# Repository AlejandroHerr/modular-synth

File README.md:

# Modular Synth

KiCad designs for DIY Eurorack modular synthesizer modules.

## Acknowledgements

This project is based on the work of [Erica Synths](https://www.ericasynths.lv/) and [Moritz Klein](https://www.youtube.com/@MoritzKlein0), in particular their collaboration on the **mki x es.EDU** DIY series: nine educational kits (sequencer, VCO, wavefolder, noise/S&H, mixer, VCF, envelope generator, dual VCA, and output stereo mixer with headphone amp) that walk through the design of analog synth circuits step by step. The VCO was the first kit released.

Moritz Klein's YouTube series explaining the circuit design is the main reference. All credit for the original circuit designs goes to them.

## Contents

- `vco/`: KiCad project for a sawtooth-core analog VCO (schematic and PCB), with a separate power block schematic.
- `vcf/`: KiCad project for a VCF (schematic and PCB).
- `envelope-generator/`: KiCad project for an envelope generator (schematic only for now, the PCB is not laid out yet).

## References

- [Erica Synths and Moritz Klein set to release DIY synthesiser kits (Mixdown)](https://mixdownmag.com.au/news/erica-synths-and-moritz-klein-set-to-release-diy-synthesiser-kits/)
- [Erica Synths mki x es.EDU VCO (Synth Anatomy)](https://www.synthanatomy.com/2021/12/mki-x-es-edu-vco-first-education-diy-module-from-erica-synths-and-moritz-klein.html)
- [DIY Eurorack series kicks off with Erica Synths and Moritz Klein (CDM)](https://cdm.link/2022/01/diy-eurorack-series-kicks-off-with-erica-synths-and-moritz-klein-mki-x-es-edu/)

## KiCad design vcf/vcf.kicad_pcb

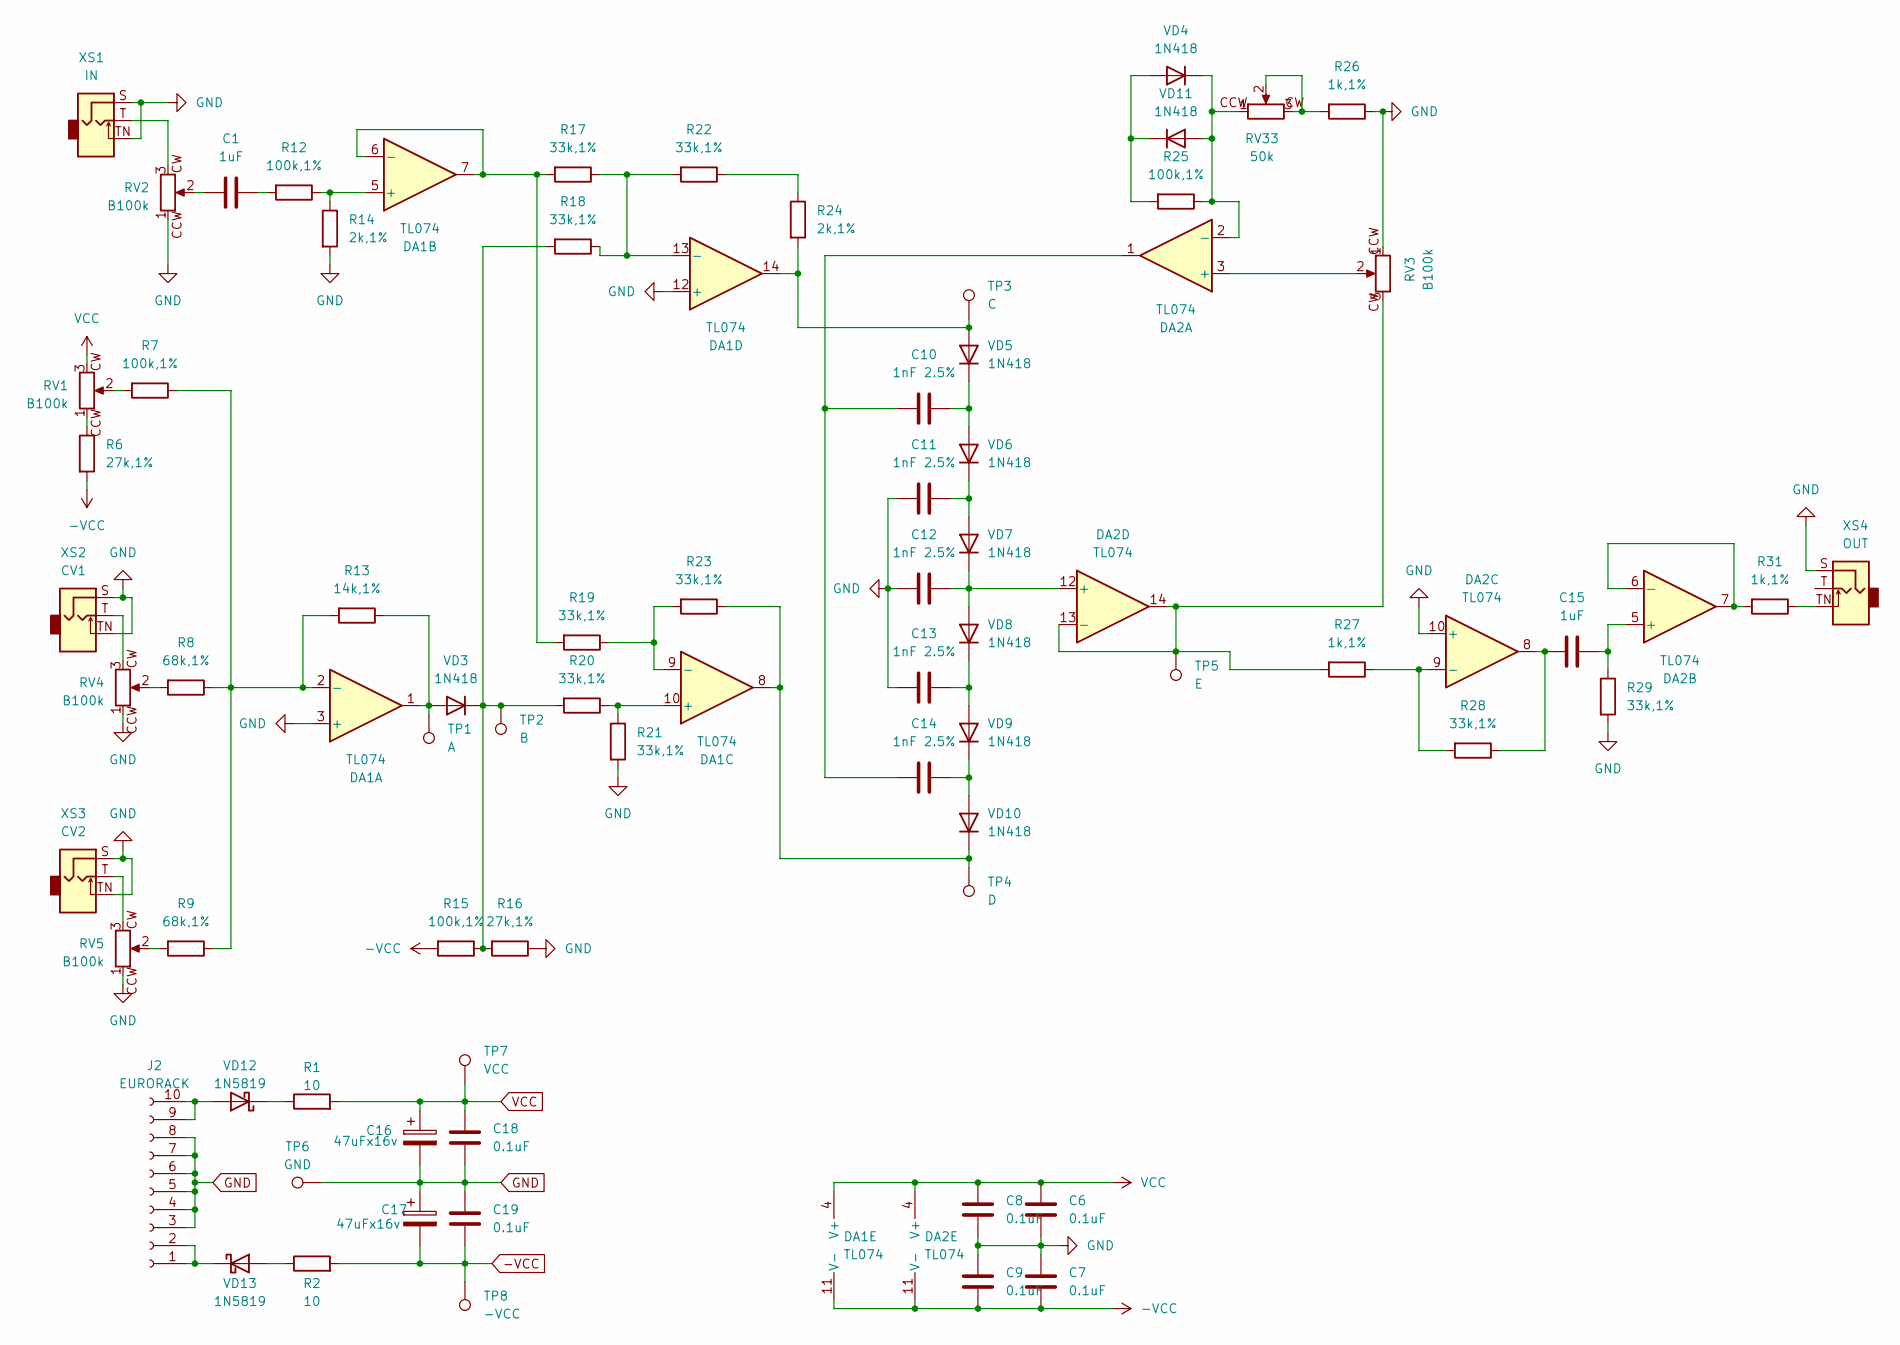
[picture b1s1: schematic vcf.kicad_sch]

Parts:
C1, C15: 1uF; C_Rect_L7.2mm_W6.0mm_P5.00mm
C6, C7, C8, C9: 0.1uF; C_Disc_D4.7mm_W2.5mm_P5.00mm
C10, C11, C12, C13, C14: 1nF 2.5%; C_Rect_L7.2mm_W6.0mm_P5.00mm
C16, C17: 47uFx16v; CP_Radial_D5.0mm_P2.00mm
C18, C19: 0.1uF; C_Rect_L4.0mm_W2.5mm_P2.50mm
DA1, DA2: TL074; DIP-14_W7.62mm_Socket
J2: EURORACK; IDC-Header_2x05_P2.54mm_Vertical-NoSign
R1, R2: 10; R_Axial_DIN0207_L6.3mm_D2.5mm_P10.16mm_Horizontal
R6, R16: 27k,1%; R_Axial_DIN0207_L6.3mm_D2.5mm_P10.16mm_Horizontal
R7, R12, R15, R25: 100k,1%; R_Axial_DIN0207_L6.3mm_D2.5mm_P10.16mm_Horizontal
R8, R9: 68k,1%; R_Axial_DIN0207_L6.3mm_D2.5mm_P10.16mm_Horizontal
R13: 14k,1%; R_Axial_DIN0207_L6.3mm_D2.5mm_P10.16mm_Horizontal
R14, R24: 2k,1%; R_Axial_DIN0207_L6.3mm_D2.5mm_P10.16mm_Horizontal
R17, R18, R19, R20, R21, R22, R23, R28, R29: 33k,1%; R_Axial_DIN0207_L6.3mm_D2.5mm_P10.16mm_Horizontal
R26, R27, R31: 1k,1%; R_Axial_DIN0207_L6.3mm_D2.5mm_P10.16mm_Horizontal
RV1, RV2, RV3, RV4, RV5: B100k; Alpha POT Original
RV33: 50k; Potentiometer_Vishay_T93YA_Vertical
TP1: A; TestPoint_Keystone_5000-5004_Miniature
TP2: B; TestPoint_Keystone_5000-5004_Miniature
TP3: C; TestPoint_Keystone_5000-5004_Miniature
TP4: D; TestPoint_Keystone_5000-5004_Miniature
TP5: E; TestPoint_Keystone_5000-5004_Miniature
TP6: GND; TestPoint_Keystone_5000-5004_Miniature
TP7: VCC; TestPoint_Keystone_5000-5004_Miniature
TP8: -VCC; TestPoint_Keystone_5000-5004_Miniature
VD3, VD4, VD5, VD6, VD7, VD8, VD9, VD10, VD11: 1N418; D_DO-35_SOD27_P7.62mm_Horizontal
VD12, VD13: 1N5819; D_DO-41_SOD81_P7.62mm_Horizontal
XS1: IN; Jack_3.5mm_QingPu_WQP-PJ398SM_Vertical_CircularHoles_3d
XS2: CV1; Jack_3.5mm_QingPu_WQP-PJ398SM_Vertical_CircularHoles_3d
XS3: CV2; Jack_3.5mm_QingPu_WQP-PJ398SM_Vertical_CircularHoles_3d
XS4: OUT; Jack_3.5mm_QingPu_WQP-PJ398SM_Vertical_CircularHoles_3d

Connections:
-VCC: C7.2, C9.2, C17.2, C19.2, DA1.11 (V-), DA2.11 (V-), R2.2, R6.2, R15.2, TP8.1 (1_1)
GND: C6.2, C7.1, C8.2, C9.1, C11.2, C12.2, C13.2, C16.2, C17.1, C18.2, C19.1, DA1.3 (+), DA1.12 (+), DA2.10 (+), J2.3, J2.4, J2.5, J2.6, J2.7, J2.8, R14.2, R16.1, R21.2, R26.1, R29.2, RV2.1 (CCW), RV3.1 (CCW), RV4.1 (CCW), RV5.1 (CCW), TP6.1 (1_1), XS1.S, XS1.TN, XS2.S, XS2.TN, XS3.S, XS3.TN, XS4.S
unnamed: C1.1, RV2.2
unnamed: C1.2, R12.2
unnamed: C10.2, C14.2, DA2.1
unnamed: C15.1, DA2.8, R28.1
unnamed: DA1.2 (-), R7.1, R8.1, R9.1, R13.2
unnamed: DA1.5 (+), R12.1, R14.1
unnamed: DA1.6 (-), DA1.7, R17.2, R19.2
unnamed: DA1.10 (+), R20.1, R21.1
unnamed: DA1.9 (-), R19.1, R23.2
unnamed: DA1.13 (-), R17.1, R18.1, R22.2
unnamed: DA2.3 (+), RV3.2
unnamed: DA2.2 (-), R25.1, RV33.1 (CCW), VD4.1 (K), VD11.2 (A)
unnamed: C15.2, DA2.5 (+), R29.1
unnamed: DA2.6 (-), DA2.7, R31.2
unnamed: DA2.9 (-), R27.1, R28.2
unnamed: C12.1, DA2.12 (+), VD7.1 (K), VD8.2 (A)
unnamed: DA2.13 (-), DA2.14, R27.2, RV3.3 (CW), TP5.1 (1_1)
unnamed: J2.1, J2.2, VD13.1 (K)
unnamed: J2.9, J2.10, VD12.2 (A)
unnamed: R7.2, RV1.2
unnamed: R8.2, RV4.2
unnamed: R9.2, RV5.2
unnamed: R22.1, R24.1
unnamed: R31.1, XS4.TN
unnamed: R6.1, RV1.1 (CCW)
unnamed: RV2.3 (CW), XS1.T
unnamed: RV4.3 (CW), XS2.T
unnamed: RV5.3 (CW), XS3.T
unnamed: R26.2, RV33.2, RV33.3 (CW)
unnamed: DA1.1, R13.1, TP1.1 (1_1), VD3.2 (A)
unnamed: R15.1, R16.2, R18.2, R20.2, TP2.1 (1_1), VD3.1 (K)
unnamed: DA1.14, R24.2, TP3.1 (1_1), VD5.2 (A)
unnamed: C10.1, VD5.1 (K), VD6.2 (A)
unnamed: C11.1, VD6.1 (K), VD7.2 (A)
unnamed: C13.1, VD8.1 (K), VD9.2 (A)
unnamed: C14.1, VD9.1 (K), VD10.2 (A)
unnamed: DA1.8, R23.1, TP4.1 (1_1), VD10.1 (K)
unnamed: R25.2, VD4.2 (A), VD11.1 (K)
unnamed: R1.1, VD12.1 (K)
unnamed: R2.1, VD13.2 (A)
VCC: C6.1, C8.1, C16.1, C18.1, DA1.4 (V+), DA2.4 (V+), R1.2, RV1.3 (CW), TP7.1 (1_1)

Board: 4 copper layers, 72 parts (9 on the bottom side), 43 nets, no tracks yet.

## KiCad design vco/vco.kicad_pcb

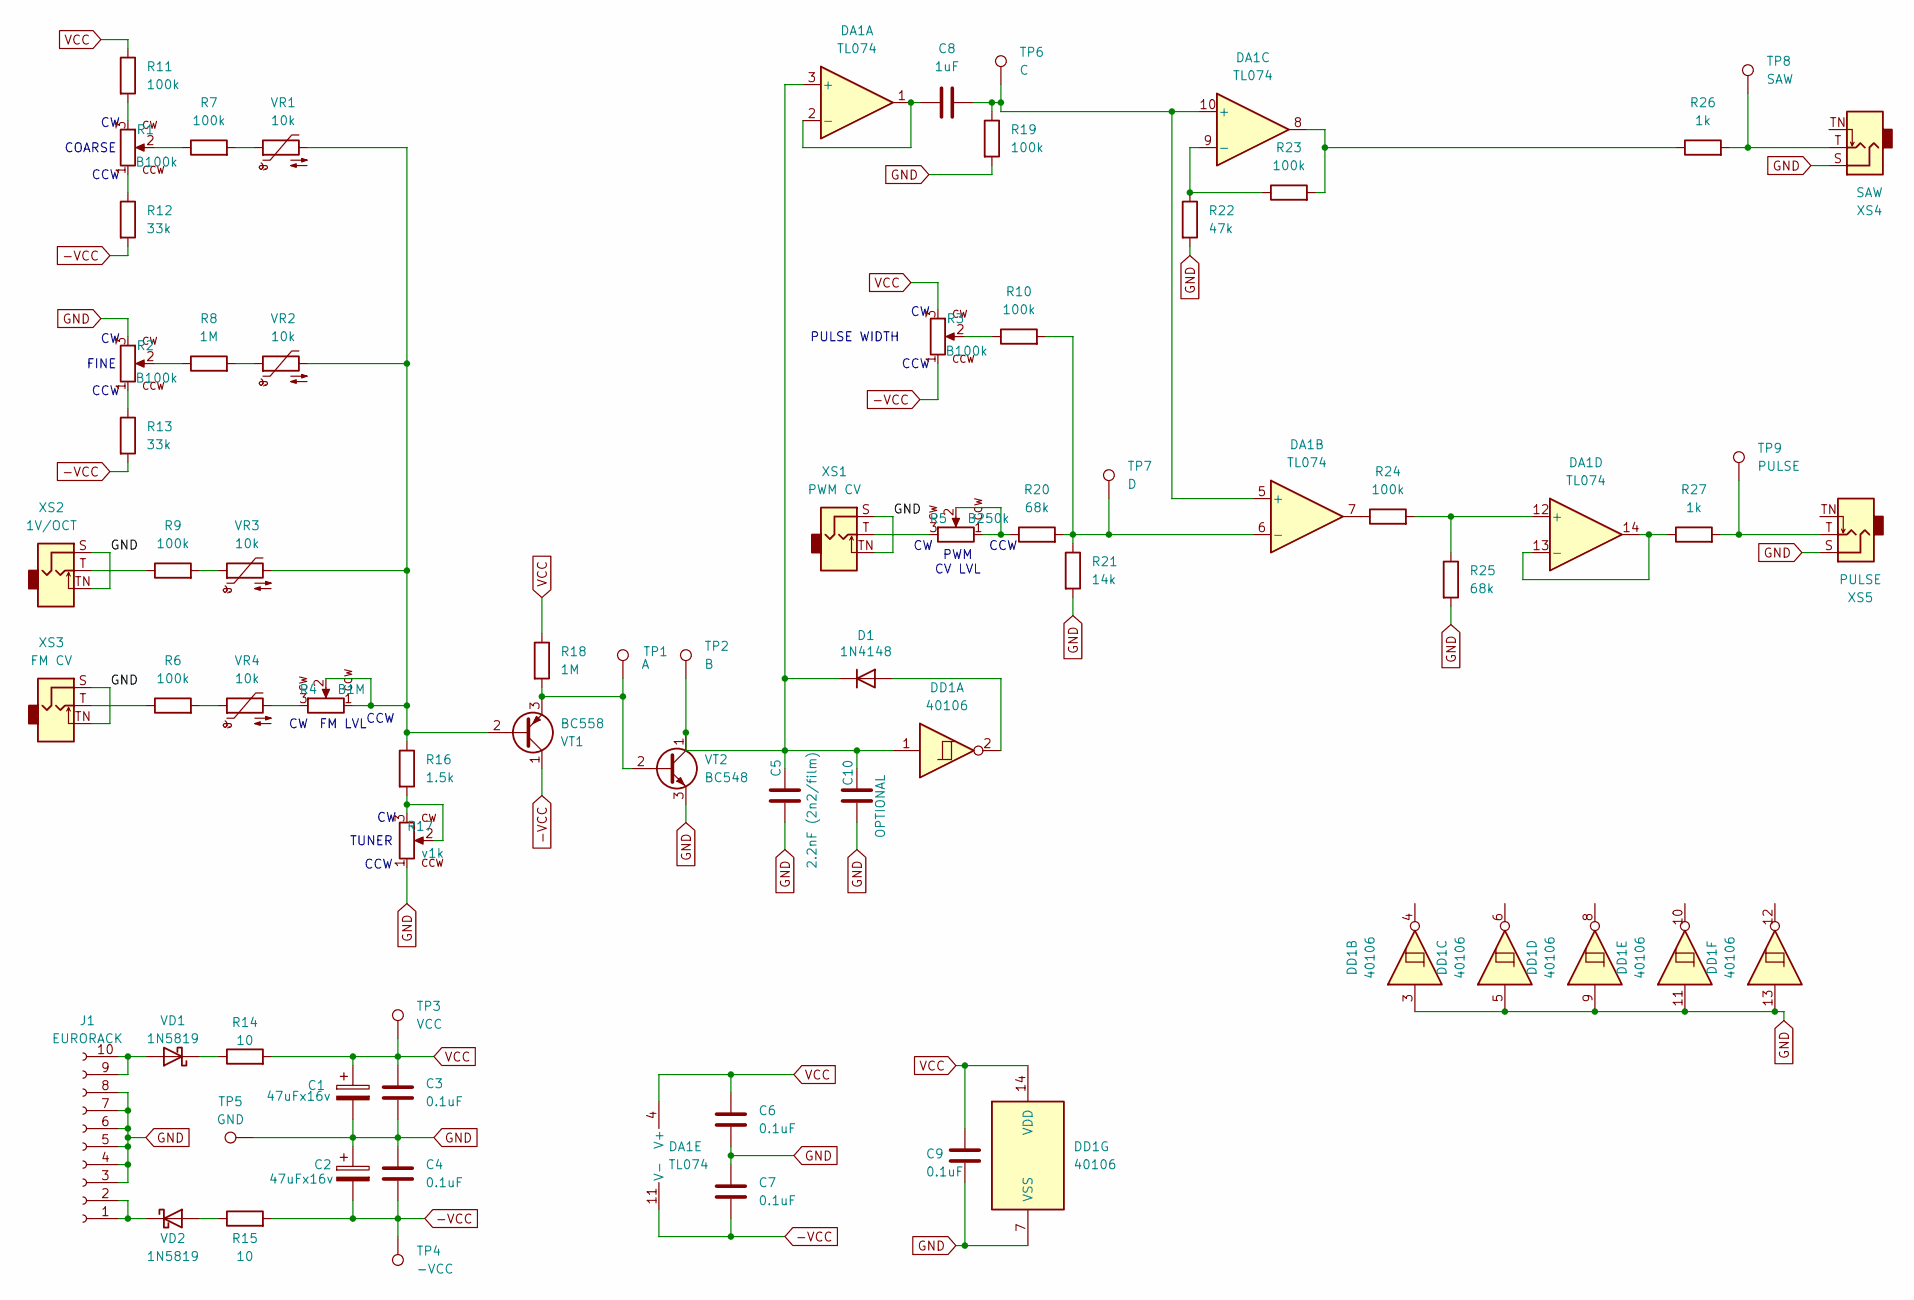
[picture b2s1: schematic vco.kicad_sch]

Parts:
C1, C2: 47uFx16v; CP_Radial_D5.0mm_P2.00mm
C3, C4, C6, C7, C9: 0.1uF; C_Rect_L4.0mm_W2.5mm_P2.50mm
C5: 2.2nF (2n2/film); C_Rect_L7.2mm_W2.5mm_P5.00mm_FKS2_FKP2_MKS2_MKP2
C8: 1uF; C_Rect_L13.5mm_W5.0mm_P10.00mm_FKS3_FKP3_MKS4
C10: OPTIONAL
D1: 1N4148; D_DO-35_SOD27_P7.62mm_Horizontal
DA1: TL074; DIP-14_W7.62mm_Socket
DD1: 40106; DIP-14_W7.62mm_Socket
J1: EURORACK; IDC-Header_2x05_P2.54mm_Vertical-NoSign
R1, R2, R3: B100k; Alpha POT Original
R4: B1M; Alpha POT Original
R5: B250k; Alpha POT Original
R6, R7, R9, R10, R19, R23, R24: 100k; R_Axial_DIN0207_L6.3mm_D2.5mm_P10.16mm_Horizontal
R8, R18: 1M; R_Axial_DIN0207_L6.3mm_D2.5mm_P10.16mm_Horizontal
R11: 100k; R_Axial_DIN0207_L6.3mm_D2.5mm_P2.54mm_Vertical
R12: 33k; R_Axial_DIN0207_L6.3mm_D2.5mm_P2.54mm_Vertical
R13: 33k; R_Axial_DIN0207_L6.3mm_D2.5mm_P10.16mm_Horizontal
R14, R15: 10; R_Axial_DIN0207_L6.3mm_D2.5mm_P10.16mm_Horizontal
R16: 1.5k; R_Axial_DIN0207_L6.3mm_D2.5mm_P10.16mm_Horizontal
R17: v1k; Alpha POT Original
R20, R25: 68k; R_Axial_DIN0207_L6.3mm_D2.5mm_P10.16mm_Horizontal
R21: 14k; R_Axial_DIN0207_L6.3mm_D2.5mm_P2.54mm_Vertical
R22: 47k; R_Axial_DIN0207_L6.3mm_D2.5mm_P10.16mm_Horizontal
R26, R27: 1k; R_Axial_DIN0207_L6.3mm_D2.5mm_P10.16mm_Horizontal
TP1: A; TestPoint_Keystone_5000-5004_Miniature
TP2: B; TestPoint_Keystone_5000-5004_Miniature
TP3: VCC; TestPoint_Keystone_5000-5004_Miniature
TP4: -VCC; TestPoint_Keystone_5000-5004_Miniature
TP5: GND; TestPoint_Keystone_5000-5004_Miniature
TP6: C; TestPoint_Keystone_5000-5004_Miniature
TP7: D; TestPoint_Keystone_5000-5004_Miniature
TP8: SAW; TestPoint_Keystone_5000-5004_Miniature
TP9: PULSE; TestPoint_Keystone_5000-5004_Miniature
VD1, VD2: 1N5819; D_DO-41_SOD81_P7.62mm_Horizontal
VR1, VR2, VR3, VR4: 10k; R_Axial_DIN0204_L3.6mm_D1.6mm_P2.54mm_Vertical
VT1: BC558; TO-92_Inline
VT2: BC548; TO-92_Inline
XS1: PWM CV; Jack_3.5mm_QingPu_WQP-PJ398SM_Vertical_CircularHoles_3d
XS2: 1V/OCT; Jack_3.5mm_QingPu_WQP-PJ398SM_Vertical_CircularHoles_3d
XS3: FM CV; Jack_3.5mm_QingPu_WQP-PJ398SM_Vertical_CircularHoles_3d
XS4: SAW; Jack_3.5mm_QingPu_WQP-PJ398SM_Vertical_CircularHoles_3d
XS5: PULSE; Jack_3.5mm_QingPu_WQP-PJ398SM_Vertical_CircularHoles_3d

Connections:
-VCC: C2.2, C4.2, C7.2, DA1.11 (V-), R3.1 (CCW), R12.2, R13.2, R15.2, TP4.1 (1_1), VT1.1 (C)
GND: C1.2, C2.1, C3.2, C4.1, C5.2, C6.2, C7.1, C9.2, C10.2, DD1.3, DD1.5, DD1.7 (VSS), DD1.9, DD1.11, DD1.13, J1.3, J1.4, J1.5, J1.6, J1.7, J1.8, R2.3 (CW), R17.1 (CCW), R19.2, R21.2, R22.2, R25.2, TP5.1 (1_1), VT2.3 (E), XS1.S, XS1.TN, XS2.S, XS2.TN, XS3.S, XS3.TN, XS4.S, XS5.S
unnamed: D1.2 (A), DD1.2
unnamed: C5.1, C10.1, D1.1 (K), DA1.3 (+), DD1.1, TP2.1 (1_1), VT2.1 (C)
unnamed: DA1.7, R24.1
unnamed: DA1.8, R23.2, R26.1
unnamed: C8.1, DA1.1, DA1.2 (-)
unnamed: C8.2, DA1.5 (+), DA1.10 (+), R19.1, TP6.1 (1_1)
unnamed: DA1.6 (-), R10.2, R20.2, R21.1, TP7.1 (1_1)
unnamed: DA1.9 (-), R22.1, R23.1
unnamed: DA1.12 (+), R24.2, R25.1
unnamed: DA1.13 (-), DA1.14, R27.1
unnamed: J1.1, J1.2, VD2.1 (K)
unnamed: J1.9, J1.10, VD1.2 (A)
unnamed: R1.1 (CCW), R12.1
unnamed: R1.3 (CW), R11.2
unnamed: R1.2 (W), R7.1
unnamed: R2.2 (W), R8.1
unnamed: R4.3 (CW), VR4.2
unnamed: R5.3 (CW), XS1.T
unnamed: R6.1, XS3.T
unnamed: R6.2, VR4.1
unnamed: R7.2, VR1.1
unnamed: R8.2, VR2.1
unnamed: R9.1, XS2.T
unnamed: R9.2, VR3.1
unnamed: R3.2 (W), R10.1
unnamed: R2.1 (CCW), R13.1
unnamed: R16.2, R17.2 (W), R17.3 (CW)
unnamed: R5.1 (CCW), R5.2 (W), R20.1
unnamed: R26.2, TP8.1 (1_1), XS4.T
unnamed: R27.2, TP9.1 (1_1), XS5.T
unnamed: R14.1, VD1.1 (K)
unnamed: R15.1, VD2.2 (A)
unnamed: R4.1 (CCW), R4.2 (W), R16.1, VR1.2, VR2.2, VR3.2, VT1.2 (B)
unnamed: R18.2, TP1.1 (1_1), VT1.3 (E), VT2.2 (B)
VCC: C1.1, C3.1, C6.1, C9.1, DA1.4 (V+), DD1.14 (VDD), R3.3 (CW), R11.1, R14.2, R18.1, TP3.1 (1_1)

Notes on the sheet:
FM LVL
PULSE WIDTH
CCW
TUNER
FINE
PWM CV LVL
COARSE

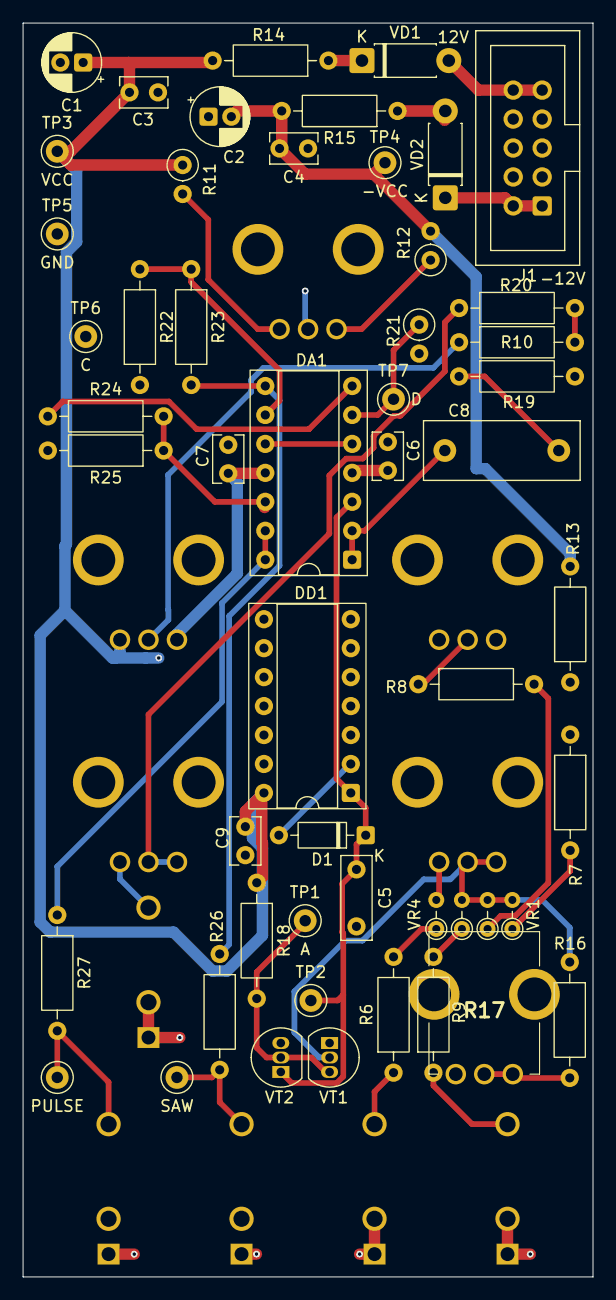
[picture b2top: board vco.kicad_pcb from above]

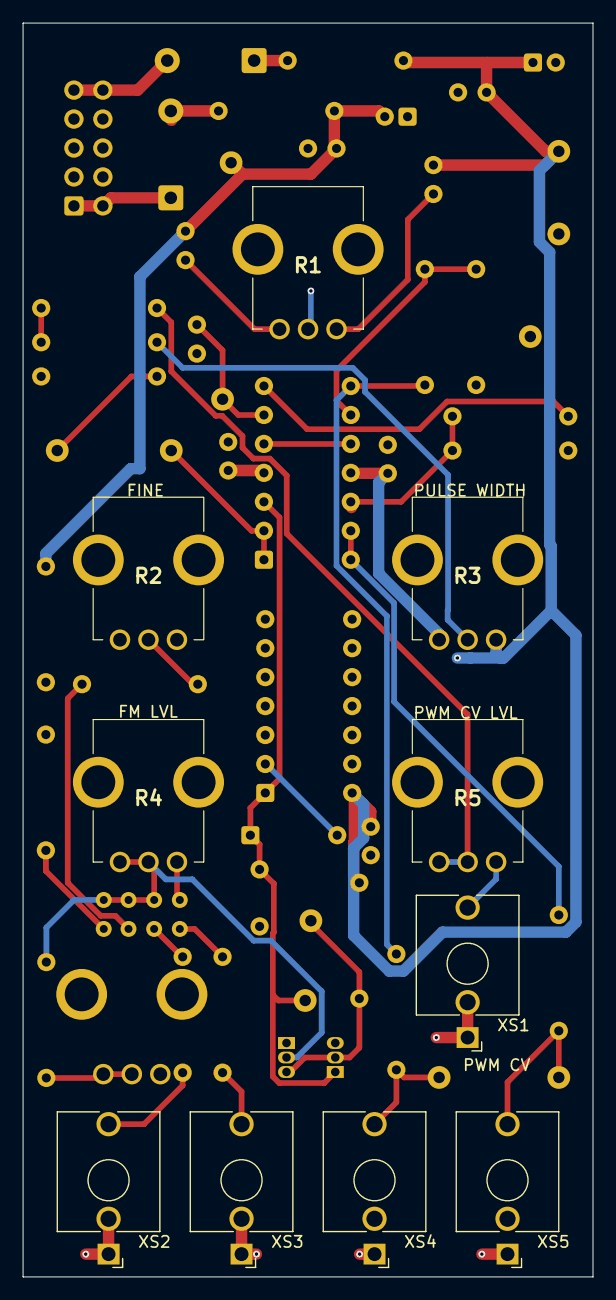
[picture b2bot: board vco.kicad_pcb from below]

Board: 4 copper layers, 50.0 x 110.0 mm, 62 parts (10 on the bottom side), 37 nets.
